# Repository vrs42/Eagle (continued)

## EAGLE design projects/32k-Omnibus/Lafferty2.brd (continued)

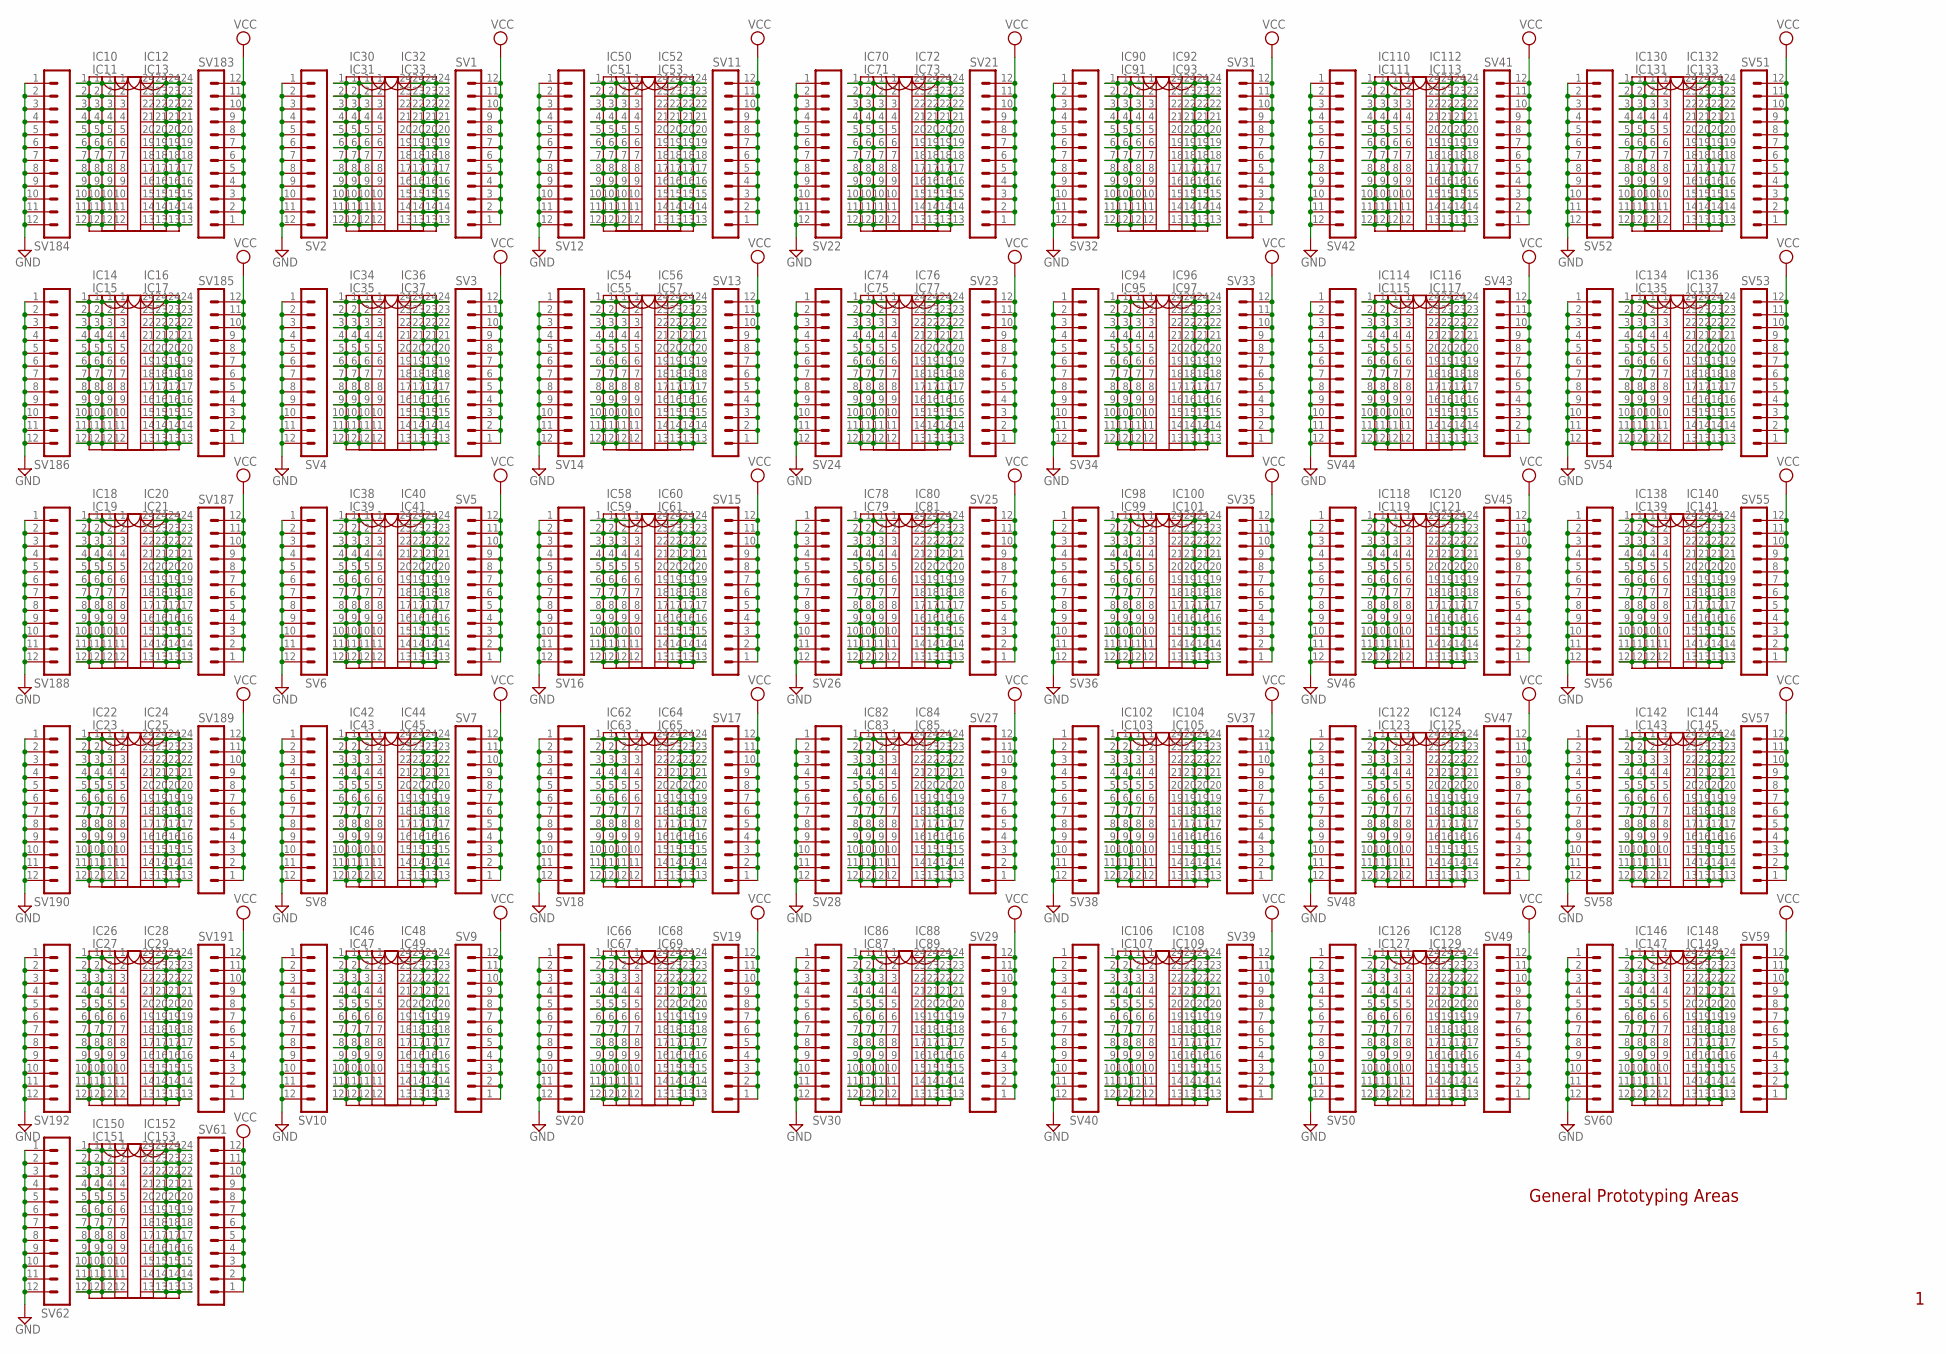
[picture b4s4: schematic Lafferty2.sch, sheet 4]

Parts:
IC10, IC14, IC18, IC22, IC26, IC30, IC34, IC38, IC42, IC46, IC50, IC54, IC58, IC62, IC66, IC70, IC74, IC78, IC82, IC86, IC90, IC94, IC98, IC102, IC106, IC110, IC114, IC118, IC122, IC126, IC130, IC134, IC138, IC142, IC146, IC150: DIL24-3
IC11, IC13, IC15, IC17, IC19, IC21, IC23, IC25, IC27, IC29, IC31, IC33, IC35, IC37, IC39, IC41, IC43, IC45, IC47, IC49, IC51, IC53, IC55, IC57, IC59, IC61, IC63, IC65, IC67, IC69, IC71, IC73, IC75, IC77, IC79, IC81, IC83, IC85, IC87, IC89, IC91, IC93, IC95, IC97, IC99, IC101, IC103, IC105, IC107, IC109, IC111, IC113, IC115, IC117, IC119, IC121, IC123, IC125, IC127, IC129, IC131, IC133, IC135, IC137, IC139, IC141, IC143, IC145, IC147, IC149, IC151, IC153: DIL24-6
IC12, IC16, IC20, IC24, IC28, IC32, IC36, IC40, IC44, IC48, IC52, IC56, IC60, IC64, IC68, IC72, IC76, IC80, IC84, IC88, IC92, IC96, IC100, IC104, IC108, IC112, IC116, IC120, IC124, IC128, IC132, IC136, IC140, IC144, IC148, IC152: DIL24-9
SV1, SV2, SV3, SV4, SV5, SV6, SV7, SV8, SV9, SV10, SV11, SV12, SV13, SV14, SV15, SV16, SV17, SV18, SV19, SV20, SV21, SV22, SV23, SV24, SV25, SV26, SV27, SV28, SV29, SV30, SV31, SV32, SV33, SV34, SV35, SV36, SV37, SV38, SV39, SV40, SV41, SV42, SV43, SV44, SV45, SV46, SV47, SV48, SV49, SV50, SV51, SV52, SV53, SV54, SV55, SV56, SV57, SV58, SV59, SV60, SV61, SV62, SV183, SV184, SV185, SV186, SV187, SV188, SV189, SV190, SV191, SV192: MA12-1

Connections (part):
GND: SV2.1, SV2.2, SV2.3, SV2.4, SV2.5, SV2.6, SV2.7, SV2.8, SV2.9, SV2.10, SV2.11, SV2.12, SV4.1, SV4.2, SV4.3, SV4.4, SV4.5, SV4.6, SV4.7, SV4.8, SV4.9, SV4.10, SV4.11, SV4.12, SV6.1, SV6.2, SV6.3, SV6.4, SV6.5, SV6.6, SV6.7, SV6.8, SV6.9, SV6.10, SV6.11, SV6.12, SV8.1, SV8.2, SV8.3, SV8.4, SV8.5, SV8.6, SV8.7, SV8.8, SV8.9, SV8.10, SV8.11, SV8.12, SV10.1, SV10.2, SV10.3, SV10.4, SV10.5, SV10.6, SV10.7, SV10.8, SV10.9, SV10.10, SV10.11, SV10.12, SV12.1, SV12.2, SV12.3, SV12.4, SV12.5, SV12.6, SV12.7, SV12.8, SV12.9, SV12.10, SV12.11, SV12.12, SV14.1, SV14.2, SV14.3, SV14.4, SV14.5, SV14.6, SV14.7, SV14.8, SV14.9, SV14.10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; also elsewhere on the board
unnamed: IC30.1, IC31.1, IC32.1, IC33.1
unnamed: IC30.2, IC31.2, IC32.2, IC33.2
unnamed: IC30.3, IC31.3, IC32.3, IC33.3
unnamed: IC30.4, IC31.4, IC32.4, IC33.4
unnamed: IC30.5, IC31.5, IC32.5, IC33.5
unnamed: IC30.6, IC31.6, IC32.6, IC33.6
unnamed: IC30.7, IC31.7, IC32.7, IC33.7
unnamed: IC10.1, IC11.1, IC12.1, IC13.1
unnamed: IC10.2, IC11.2, IC12.2, IC13.2
unnamed: IC10.3, IC11.3, IC12.3, IC13.3
unnamed: IC10.4, IC11.4, IC12.4, IC13.4
unnamed: IC10.5, IC11.5, IC12.5, IC13.5
unnamed: IC10.6, IC11.6, IC12.6, IC13.6
unnamed: IC10.7, IC11.7, IC12.7, IC13.7
unnamed: IC10.8, IC11.8, IC12.8, IC13.8
unnamed: IC10.9, IC11.9, IC12.9, IC13.9
unnamed: IC10.10, IC11.10, IC12.10, IC13.10
unnamed: IC10.11, IC11.11, IC12.11, IC13.11
unnamed: IC10.12, IC11.12, IC12.12, IC13.12
unnamed: IC10.13, IC11.13, IC12.13, IC13.13
unnamed: IC10.14, IC11.14, IC12.14, IC13.14
unnamed: IC10.15, IC11.15, IC12.15, IC13.15
unnamed: IC10.16, IC11.16, IC12.16, IC13.16
unnamed: IC10.17, IC11.17, IC12.17, IC13.17
unnamed: IC10.18, IC11.18, IC12.18, IC13.18
unnamed: IC10.19, IC11.19, IC12.19, IC13.19
unnamed: IC10.20, IC11.20, IC12.20, IC13.20
unnamed: IC10.21, IC11.21, IC12.21, IC13.21
unnamed: IC10.22, IC11.22, IC12.22, IC13.22
unnamed: IC10.23, IC11.23, IC12.23, IC13.23
unnamed: IC10.24, IC11.24, IC12.24, IC13.24
unnamed: IC14.1, IC15.1, IC16.1, IC17.1
unnamed: IC14.2, IC15.2, IC16.2, IC17.2
unnamed: IC14.3, IC15.3, IC16.3, IC17.3
unnamed: IC14.4, IC15.4, IC16.4, IC17.4
unnamed: IC14.5, IC15.5, IC16.5, IC17.5
unnamed: IC14.6, IC15.6, IC16.6, IC17.6
unnamed: IC14.7, IC15.7, IC16.7, IC17.7
unnamed: IC14.8, IC15.8, IC16.8, IC17.8
unnamed: IC14.9, IC15.9, IC16.9, IC17.9
unnamed: IC14.10, IC15.10, IC16.10, IC17.10
unnamed: IC14.11, IC15.11, IC16.11, IC17.11
unnamed: IC14.12, IC15.12, IC16.12, IC17.12
unnamed: IC14.13, IC15.13, IC16.13, IC17.13
unnamed: IC14.14, IC15.14, IC16.14, IC17.14
unnamed: IC14.15, IC15.15, IC16.15, IC17.15
unnamed: IC14.16, IC15.16, IC16.16, IC17.16
unnamed: IC14.17, IC15.17, IC16.17, IC17.17
unnamed: IC14.18, IC15.18, IC16.18, IC17.18
unnamed: IC14.19, IC15.19, IC16.19, IC17.19
unnamed: IC14.20, IC15.20, IC16.20, IC17.20
unnamed: IC14.21, IC15.21, IC16.21, IC17.21
unnamed: IC14.22, IC15.22, IC16.22, IC17.22
unnamed: IC14.23, IC15.23, IC16.23, IC17.23
unnamed: IC14.24, IC15.24, IC16.24, IC17.24
unnamed: IC18.1, IC19.1, IC20.1, IC21.1
unnamed: IC18.2, IC19.2, IC20.2, IC21.2
unnamed: IC18.3, IC19.3, IC20.3, IC21.3
unnamed: IC18.4, IC19.4, IC20.4, IC21.4
unnamed: IC18.5, IC19.5, IC20.5, IC21.5
unnamed: IC18.6, IC19.6, IC20.6, IC21.6
unnamed: IC18.7, IC19.7, IC20.7, IC21.7
unnamed: IC18.8, IC19.8, IC20.8, IC21.8
unnamed: IC18.9, IC19.9, IC20.9, IC21.9
unnamed: IC18.10, IC19.10, IC20.10, IC21.10
unnamed: IC18.11, IC19.11, IC20.11, IC21.11
unnamed: IC18.12, IC19.12, IC20.12, IC21.12
unnamed: IC18.13, IC19.13, IC20.13, IC21.13
unnamed: IC18.14, IC19.14, IC20.14, IC21.14
unnamed: IC18.15, IC19.15, IC20.15, IC21.15
unnamed: IC18.16, IC19.16, IC20.16, IC21.16
unnamed: IC18.17, IC19.17, IC20.17, IC21.17
unnamed: IC18.18, IC19.18, IC20.18, IC21.18
unnamed: IC18.19, IC19.19, IC20.19, IC21.19
unnamed: IC18.20, IC19.20, IC20.20, IC21.20
unnamed: IC18.21, IC19.21, IC20.21, IC21.21
unnamed: IC18.22, IC19.22, IC20.22, IC21.22
unnamed: IC18.23, IC19.23, IC20.23, IC21.23
unnamed: IC18.24, IC19.24, IC20.24, IC21.24
unnamed: IC22.1, IC23.1, IC24.1, IC25.1
unnamed: IC22.2, IC23.2, IC24.2, IC25.2
unnamed: IC22.3, IC23.3, IC24.3, IC25.3
unnamed: IC22.4, IC23.4, IC24.4, IC25.4
unnamed: IC22.5, IC23.5, IC24.5, IC25.5
unnamed: IC22.6, IC23.6, IC24.6, IC25.6
unnamed: IC22.7, IC23.7, IC24.7, IC25.7
unnamed: IC22.8, IC23.8, IC24.8, IC25.8
unnamed: IC22.9, IC23.9, IC24.9, IC25.9
unnamed: IC22.10, IC23.10, IC24.10, IC25.10
unnamed: IC22.11, IC23.11, IC24.11, IC25.11
unnamed: IC22.12, IC23.12, IC24.12, IC25.12
unnamed: IC22.13, IC23.13, IC24.13, IC25.13
unnamed: IC22.14, IC23.14, IC24.14, IC25.14
unnamed: IC22.15, IC23.15, IC24.15, IC25.15
unnamed: IC22.16, IC23.16, IC24.16, IC25.16
unnamed: IC22.17, IC23.17, IC24.17, IC25.17
unnamed: IC22.18, IC23.18, IC24.18, IC25.18
unnamed: IC22.19, IC23.19, IC24.19, IC25.19
unnamed: IC22.20, IC23.20, IC24.20, IC25.20
unnamed: IC22.21, IC23.21, IC24.21, IC25.21
unnamed: IC22.22, IC23.22, IC24.22, IC25.22
unnamed: IC22.23, IC23.23, IC24.23, IC25.23
unnamed: IC22.24, IC23.24, IC24.24, IC25.24
unnamed: IC26.1, IC27.1, IC28.1, IC29.1
unnamed: IC26.2, IC27.2, IC28.2, IC29.2
unnamed: IC26.3, IC27.3, IC28.3, IC29.3
unnamed: IC26.4, IC27.4, IC28.4, IC29.4
unnamed: IC26.5, IC27.5, IC28.5, IC29.5
unnamed: IC26.6, IC27.6, IC28.6, IC29.6
unnamed: IC26.7, IC27.7, IC28.7, IC29.7
unnamed: IC26.8, IC27.8, IC28.8, IC29.8
unnamed: IC26.9, IC27.9, IC28.9, IC29.9
unnamed: IC26.10, IC27.10, IC28.10, IC29.10
unnamed: IC26.11, IC27.11, IC28.11, IC29.11
unnamed: IC26.12, IC27.12, IC28.12, IC29.12
unnamed: IC26.13, IC27.13, IC28.13, IC29.13
unnamed: IC26.14, IC27.14, IC28.14, IC29.14
unnamed: IC26.15, IC27.15, IC28.15, IC29.15
unnamed: IC26.16, IC27.16, IC28.16, IC29.16
unnamed: IC26.17, IC27.17, IC28.17, IC29.17
unnamed: IC26.18, IC27.18, IC28.18, IC29.18
unnamed: IC26.19, IC27.19, IC28.19, IC29.19
unnamed: IC26.20, IC27.20, IC28.20, IC29.20
unnamed: IC26.21, IC27.21, IC28.21, IC29.21
unnamed: IC26.22, IC27.22, IC28.22, IC29.22
unnamed: IC26.23, IC27.23, IC28.23, IC29.23
unnamed: IC26.24, IC27.24, IC28.24, IC29.24
unnamed: IC30.8, IC31.8, IC32.8, IC33.8
unnamed: IC30.9, IC31.9, IC32.9, IC33.9
unnamed: IC30.10, IC31.10, IC32.10, IC33.10
unnamed: IC30.11, IC31.11, IC32.11, IC33.11
unnamed: IC30.12, IC31.12, IC32.12, IC33.12
unnamed: IC30.13, IC31.13, IC32.13, IC33.13
unnamed: IC30.14, IC31.14, IC32.14, IC33.14
unnamed: IC30.15, IC31.15, IC32.15, IC33.15
unnamed: IC30.16, IC31.16, IC32.16, IC33.16
unnamed: IC30.17, IC31.17, IC32.17, IC33.17
unnamed: IC30.18, IC31.18, IC32.18, IC33.18
unnamed: IC30.19, IC31.19, IC32.19, IC33.19
unnamed: IC30.20, IC31.20, IC32.20, IC33.20
unnamed: IC30.21, IC31.21, IC32.21, IC33.21
unnamed: IC30.22, IC31.22, IC32.22, IC33.22
unnamed: IC30.23, IC31.23, IC32.23, IC33.23
unnamed: IC30.24, IC31.24, IC32.24, IC33.24
unnamed: IC34.1, IC35.1, IC36.1, IC37.1
unnamed: IC34.2, IC35.2, IC36.2, IC37.2
unnamed: IC34.3, IC35.3, IC36.3, IC37.3
unnamed: IC34.4, IC35.4, IC36.4, IC37.4
unnamed: IC34.5, IC35.5, IC36.5, IC37.5
unnamed: IC34.6, IC35.6, IC36.6, IC37.6
unnamed: IC34.7, IC35.7, IC36.7, IC37.7
unnamed: IC34.8, IC35.8, IC36.8, IC37.8
unnamed: IC34.9, IC35.9, IC36.9, IC37.9
unnamed: IC34.10, IC35.10, IC36.10, IC37.10
unnamed: IC34.11, IC35.11, IC36.11, IC37.11
unnamed: IC34.12, IC35.12, IC36.12, IC37.12
unnamed: IC34.13, IC35.13, IC36.13, IC37.13
unnamed: IC34.14, IC35.14, IC36.14, IC37.14
unnamed: IC34.15, IC35.15, IC36.15, IC37.15
unnamed: IC34.16, IC35.16, IC36.16, IC37.16
unnamed: IC34.17, IC35.17, IC36.17, IC37.17
unnamed: IC34.18, IC35.18, IC36.18, IC37.18
unnamed: IC34.19, IC35.19, IC36.19, IC37.19
unnamed: IC34.20, IC35.20, IC36.20, IC37.20
unnamed: IC34.21, IC35.21, IC36.21, IC37.21
unnamed: IC34.22, IC35.22, IC36.22, IC37.22
unnamed: IC34.23, IC35.23, IC36.23, IC37.23
unnamed: IC34.24, IC35.24, IC36.24, IC37.24
unnamed: IC38.1, IC39.1, IC40.1, IC41.1
unnamed: IC38.2, IC39.2, IC40.2, IC41.2
unnamed: IC38.3, IC39.3, IC40.3, IC41.3
unnamed: IC38.4, IC39.4, IC40.4, IC41.4
unnamed: IC38.5, IC39.5, IC40.5, IC41.5
unnamed: IC38.6, IC39.6, IC40.6, IC41.6
unnamed: IC38.7, IC39.7, IC40.7, IC41.7
unnamed: IC38.8, IC39.8, IC40.8, IC41.8
unnamed: IC38.9, IC39.9, IC40.9, IC41.9
unnamed: IC38.10, IC39.10, IC40.10, IC41.10
unnamed: IC38.11, IC39.11, IC40.11, IC41.11
unnamed: IC38.12, IC39.12, IC40.12, IC41.12
unnamed: IC38.13, IC39.13, IC40.13, IC41.13
unnamed: IC38.14, IC39.14, IC40.14, IC41.14
unnamed: IC38.15, IC39.15, IC40.15, IC41.15
unnamed: IC38.16, IC39.16, IC40.16, IC41.16
unnamed: IC38.17, IC39.17, IC40.17, IC41.17
unnamed: IC38.18, IC39.18, IC40.18, IC41.18
unnamed: IC38.19, IC39.19, IC40.19, IC41.19
unnamed: IC38.20, IC39.20, IC40.20, IC41.20
unnamed: IC38.21, IC39.21, IC40.21, IC41.21
unnamed: IC38.22, IC39.22, IC40.22, IC41.22
unnamed: IC38.23, IC39.23, IC40.23, IC41.23
unnamed: IC38.24, IC39.24, IC40.24, IC41.24
unnamed: IC42.1, IC43.1, IC44.1, IC45.1
unnamed: IC42.2, IC43.2, IC44.2, IC45.2
unnamed: IC42.3, IC43.3, IC44.3, IC45.3
unnamed: IC42.4, IC43.4, IC44.4, IC45.4
unnamed: IC42.5, IC43.5, IC44.5, IC45.5
unnamed: IC42.6, IC43.6, IC44.6, IC45.6
unnamed: IC42.7, IC43.7, IC44.7, IC45.7
unnamed: IC42.8, IC43.8, IC44.8, IC45.8
unnamed: IC42.9, IC43.9, IC44.9, IC45.9
unnamed: IC42.10, IC43.10, IC44.10, IC45.10
unnamed: IC42.11, IC43.11, IC44.11, IC45.11
unnamed: IC42.12, IC43.12, IC44.12, IC45.12
unnamed: IC42.13, IC43.13, IC44.13, IC45.13
unnamed: IC42.14, IC43.14, IC44.14, IC45.14
unnamed: IC42.15, IC43.15, IC44.15, IC45.15
unnamed: IC42.16, IC43.16, IC44.16, IC45.16
unnamed: IC42.17, IC43.17, IC44.17, IC45.17
unnamed: IC42.18, IC43.18, IC44.18, IC45.18
unnamed: IC42.19, IC43.19, IC44.19, IC45.19
unnamed: IC42.20, IC43.20, IC44.20, IC45.20
unnamed: IC42.21, IC43.21, IC44.21, IC45.21
unnamed: IC42.22, IC43.22, IC44.22, IC45.22
unnamed: IC42.23, IC43.23, IC44.23, IC45.23
unnamed: IC42.24, IC43.24, IC44.24, IC45.24
unnamed: IC46.1, IC47.1, IC48.1, IC49.1
unnamed: IC46.2, IC47.2, IC48.2, IC49.2
unnamed: IC46.3, IC47.3, IC48.3, IC49.3
unnamed: IC46.4, IC47.4, IC48.4, IC49.4
unnamed: IC46.5, IC47.5, IC48.5, IC49.5
unnamed: IC46.6, IC47.6, IC48.6, IC49.6
unnamed: IC46.7, IC47.7, IC48.7, IC49.7
unnamed: IC46.8, IC47.8, IC48.8, IC49.8
unnamed: IC46.9, IC47.9, IC48.9, IC49.9
unnamed: IC46.10, IC47.10, IC48.10, IC49.10
unnamed: IC46.11, IC47.11, IC48.11, IC49.11
unnamed: IC46.12, IC47.12, IC48.12, IC49.12
unnamed: IC46.13, IC47.13, IC48.13, IC49.13
unnamed: IC46.14, IC47.14, IC48.14, IC49.14
unnamed: IC46.15, IC47.15, IC48.15, IC49.15
unnamed: IC46.16, IC47.16, IC48.16, IC49.16
unnamed: IC46.17, IC47.17, IC48.17, IC49.17
unnamed: IC46.18, IC47.18, IC48.18, IC49.18
unnamed: IC46.19, IC47.19, IC48.19, IC49.19
unnamed: IC46.20, IC47.20, IC48.20, IC49.20
unnamed: IC46.21, IC47.21, IC48.21, IC49.21
unnamed: IC46.22, IC47.22, IC48.22, IC49.22
unnamed: IC46.23, IC47.23, IC48.23, IC49.23
unnamed: IC46.24, IC47.24, IC48.24, IC49.24
unnamed: IC50.1, IC51.1, IC52.1, IC53.1
unnamed: IC50.2, IC51.2, IC52.2, IC53.2
unnamed: IC50.3, IC51.3, IC52.3, IC53.3
unnamed: IC50.4, IC51.4, IC52.4, IC53.4
unnamed: IC50.5, IC51.5, IC52.5, IC53.5
unnamed: IC50.6, IC51.6, IC52.6, IC53.6
unnamed: IC50.7, IC51.7, IC52.7, IC53.7
unnamed: IC50.8, IC51.8, IC52.8, IC53.8
unnamed: IC50.9, IC51.9, IC52.9, IC53.9
unnamed: IC50.10, IC51.10, IC52.10, IC53.10
unnamed: IC50.11, IC51.11, IC52.11, IC53.11
unnamed: IC50.12, IC51.12, IC52.12, IC53.12
unnamed: IC50.13, IC51.13, IC52.13, IC53.13
unnamed: IC50.14, IC51.14, IC52.14, IC53.14
unnamed: IC50.15, IC51.15, IC52.15, IC53.15
unnamed: IC50.16, IC51.16, IC52.16, IC53.16
unnamed: IC50.17, IC51.17, IC52.17, IC53.17
unnamed: IC50.18, IC51.18, IC52.18, IC53.18
unnamed: IC50.19, IC51.19, IC52.19, IC53.19
unnamed: IC50.20, IC51.20, IC52.20, IC53.20
unnamed: IC50.21, IC51.21, IC52.21, IC53.21
unnamed: IC50.22, IC51.22, IC52.22, IC53.22
unnamed: IC50.23, IC51.23, IC52.23, IC53.23
unnamed: IC50.24, IC51.24, IC52.24, IC53.24
unnamed: IC54.1, IC55.1, IC56.1, IC57.1
unnamed: IC54.2, IC55.2, IC56.2, IC57.2
unnamed: IC54.3, IC55.3, IC56.3, IC57.3
unnamed: IC54.4, IC55.4, IC56.4, IC57.4
unnamed: IC54.5, IC55.5, IC56.5, IC57.5
unnamed: IC54.6, IC55.6, IC56.6, IC57.6
unnamed: IC54.7, IC55.7, IC56.7, IC57.7
unnamed: IC54.8, IC55.8, IC56.8, IC57.8
unnamed: IC54.9, IC55.9, IC56.9, IC57.9
unnamed: IC54.10, IC55.10, IC56.10, IC57.10
unnamed: IC54.11, IC55.11, IC56.11, IC57.11
unnamed: IC54.12, IC55.12, IC56.12, IC57.12
unnamed: IC54.13, IC55.13, IC56.13, IC57.13
unnamed: IC54.14, IC55.14, IC56.14, IC57.14
unnamed: IC54.15, IC55.15, IC56.15, IC57.15
unnamed: IC54.16, IC55.16, IC56.16, IC57.16
unnamed: IC54.17, IC55.17, IC56.17, IC57.17
unnamed: IC54.18, IC55.18, IC56.18, IC57.18
unnamed: IC54.19, IC55.19, IC56.19, IC57.19
unnamed: IC54.20, IC55.20, IC56.20, IC57.20
unnamed: IC54.21, IC55.21, IC56.21, IC57.21
unnamed: IC54.22, IC55.22, IC56.22, IC57.22
unnamed: IC54.23, IC55.23, IC56.23, IC57.23
unnamed: IC54.24, IC55.24, IC56.24, IC57.24
unnamed: IC58.1, IC59.1, IC60.1, IC61.1
unnamed: IC58.2, IC59.2, IC60.2, IC61.2
unnamed: IC58.3, IC59.3, IC60.3, IC61.3
unnamed: IC58.4, IC59.4, IC60.4, IC61.4
unnamed: IC58.5, IC59.5, IC60.5, IC61.5
unnamed: IC58.6, IC59.6, IC60.6, IC61.6
unnamed: IC58.7, IC59.7, IC60.7, IC61.7
unnamed: IC58.8, IC59.8, IC60.8, IC61.8
unnamed: IC58.9, IC59.9, IC60.9, IC61.9
unnamed: IC58.10, IC59.10, IC60.10, IC61.10
unnamed: IC58.11, IC59.11, IC60.11, IC61.11
unnamed: IC58.12, IC59.12, IC60.12, IC61.12
unnamed: IC58.13, IC59.13, IC60.13, IC61.13
unnamed: IC58.14, IC59.14, IC60.14, IC61.14
unnamed: IC58.15, IC59.15, IC60.15, IC61.15
unnamed: IC58.16, IC59.16, IC60.16, IC61.16
unnamed: IC58.17, IC59.17, IC60.17, IC61.17
unnamed: IC58.18, IC59.18, IC60.18, IC61.18
unnamed: IC58.19, IC59.19, IC60.19, IC61.19
unnamed: IC58.20, IC59.20, IC60.20, IC61.20
unnamed: IC58.21, IC59.21, IC60.21, IC61.21
unnamed: IC58.22, IC59.22, IC60.22, IC61.22
unnamed: IC58.23, IC59.23, IC60.23, IC61.23
unnamed: IC58.24, IC59.24, IC60.24, IC61.24
unnamed: IC62.1, IC63.1, IC64.1, IC65.1
unnamed: IC62.2, IC63.2, IC64.2, IC65.2
unnamed: IC62.3, IC63.3, IC64.3, IC65.3
unnamed: IC62.4, IC63.4, IC64.4, IC65.4
unnamed: IC62.5, IC63.5, IC64.5, IC65.5
unnamed: IC62.6, IC63.6, IC64.6, IC65.6
unnamed: IC62.7, IC63.7, IC64.7, IC65.7
unnamed: IC62.8, IC63.8, IC64.8, IC65.8
unnamed: IC62.9, IC63.9, IC64.9, IC65.9
unnamed: IC62.10, IC63.10, IC64.10, IC65.10
unnamed: IC62.11, IC63.11, IC64.11, IC65.11
unnamed: IC62.12, IC63.12, IC64.12, IC65.12
unnamed: IC62.13, IC63.13, IC64.13, IC65.13
unnamed: IC62.14, IC63.14, IC64.14, IC65.14
unnamed: IC62.15, IC63.15, IC64.15, IC65.15
unnamed: IC62.16, IC63.16, IC64.16, IC65.16
unnamed: IC62.17, IC63.17, IC64.17, IC65.17
unnamed: IC62.18, IC63.18, IC64.18, IC65.18
unnamed: IC62.19, IC63.19, IC64.19, IC65.19
unnamed: IC62.20, IC63.20, IC64.20, IC65.20
unnamed: IC62.21, IC63.21, IC64.21, IC65.21
unnamed: IC62.22, IC63.22, IC64.22, IC65.22
unnamed: IC62.23, IC63.23, IC64.23, IC65.23
unnamed: IC62.24, IC63.24, IC64.24, IC65.24
unnamed: IC66.1, IC67.1, IC68.1, IC69.1
unnamed: IC66.2, IC67.2, IC68.2, IC69.2
unnamed: IC66.3, IC67.3, IC68.3, IC69.3
unnamed: IC66.4, IC67.4, IC68.4, IC69.4
unnamed: IC66.5, IC67.5, IC68.5, IC69.5
unnamed: IC66.6, IC67.6, IC68.6, IC69.6
unnamed: IC66.7, IC67.7, IC68.7, IC69.7
unnamed: IC66.8, IC67.8, IC68.8, IC69.8
unnamed: IC66.9, IC67.9, IC68.9, IC69.9
unnamed: IC66.10, IC67.10, IC68.10, IC69.10
unnamed: IC66.11, IC67.11, IC68.11, IC69.11
unnamed: IC66.12, IC67.12, IC68.12, IC69.12
unnamed: IC66.13, IC67.13, IC68.13, IC69.13
unnamed: IC66.14, IC67.14, IC68.14, IC69.14
unnamed: IC66.15, IC67.15, IC68.15, IC69.15
unnamed: IC66.16, IC67.16, IC68.16, IC69.16
unnamed: IC66.17, IC67.17, IC68.17, IC69.17
unnamed: IC66.18, IC67.18, IC68.18, IC69.18
unnamed: IC66.19, IC67.19, IC68.19, IC69.19
unnamed: IC66.20, IC67.20, IC68.20, IC69.20
unnamed: IC66.21, IC67.21, IC68.21, IC69.21
unnamed: IC66.22, IC67.22, IC68.22, IC69.22
unnamed: IC66.23, IC67.23, IC68.23, IC69.23
unnamed: IC66.24, IC67.24, IC68.24, IC69.24
unnamed: IC70.1, IC71.1, IC72.1, IC73.1
unnamed: IC70.2, IC71.2, IC72.2, IC73.2
unnamed: IC70.3, IC71.3, IC72.3, IC73.3
unnamed: IC70.4, IC71.4, IC72.4, IC73.4
unnamed: IC70.5, IC71.5, IC72.5, IC73.5
unnamed: IC70.6, IC71.6, IC72.6, IC73.6
unnamed: IC70.7, IC71.7, IC72.7, IC73.7
unnamed: IC70.8, IC71.8, IC72.8, IC73.8
unnamed: IC70.9, IC71.9, IC72.9, IC73.9
unnamed: IC70.10, IC71.10, IC72.10, IC73.10
unnamed: IC70.11, IC71.11, IC72.11, IC73.11
unnamed: IC70.12, IC71.12, IC72.12, IC73.12
unnamed: IC70.13, IC71.13, IC72.13, IC73.13
unnamed: IC70.14, IC71.14, IC72.14, IC73.14
unnamed: IC70.15, IC71.15, IC72.15, IC73.15
unnamed: IC70.16, IC71.16, IC72.16, IC73.16
unnamed: IC70.17, IC71.17, IC72.17, IC73.17
unnamed: IC70.18, IC71.18, IC72.18, IC73.18
unnamed: IC70.19, IC71.19, IC72.19, IC73.19
unnamed: IC70.20, IC71.20, IC72.20, IC73.20
unnamed: IC70.21, IC71.21, IC72.21, IC73.21
unnamed: IC70.22, IC71.22, IC72.22, IC73.22
unnamed: IC70.23, IC71.23, IC72.23, IC73.23
unnamed: IC70.24, IC71.24, IC72.24, IC73.24
unnamed: IC74.1, IC75.1, IC76.1, IC77.1
unnamed: IC74.2, IC75.2, IC76.2, IC77.2
unnamed: IC74.3, IC75.3, IC76.3, IC77.3
unnamed: IC74.4, IC75.4, IC76.4, IC77.4
unnamed: IC74.5, IC75.5, IC76.5, IC77.5
unnamed: IC74.6, IC75.6, IC76.6, IC77.6
unnamed: IC74.7, IC75.7, IC76.7, IC77.7
unnamed: IC74.8, IC75.8, IC76.8, IC77.8
unnamed: IC74.9, IC75.9, IC76.9, IC77.9
unnamed: IC74.10, IC75.10, IC76.10, IC77.10
unnamed: IC74.11, IC75.11, IC76.11, IC77.11
unnamed: IC74.12, IC75.12, IC76.12, IC77.12
unnamed: IC74.13, IC75.13, IC76.13, IC77.13
unnamed: IC74.14, IC75.14, IC76.14, IC77.14
unnamed: IC74.15, IC75.15, IC76.15, IC77.15
unnamed: IC74.16, IC75.16, IC76.16, IC77.16
unnamed: IC74.17, IC75.17, IC76.17, IC77.17
unnamed: IC74.18, IC75.18, IC76.18, IC77.18
unnamed: IC74.19, IC75.19, IC76.19, IC77.19
unnamed: IC74.20, IC75.20, IC76.20, IC77.20
unnamed: IC74.21, IC75.21, IC76.21, IC77.21
unnamed: IC74.22, IC75.22, IC76.22, IC77.22
unnamed: IC74.23, IC75.23, IC76.23, IC77.23
unnamed: IC74.24, IC75.24, IC76.24, IC77.24
unnamed: IC78.1, IC79.1, IC80.1, IC81.1
unnamed: IC78.2, IC79.2, IC80.2, IC81.2
unnamed: IC78.3, IC79.3, IC80.3, IC81.3
unnamed: IC78.4, IC79.4, IC80.4, IC81.4
unnamed: IC78.5, IC79.5, IC80.5, IC81.5
unnamed: IC78.6, IC79.6, IC80.6, IC81.6
unnamed: IC78.7, IC79.7, IC80.7, IC81.7
unnamed: IC78.8, IC79.8, IC80.8, IC81.8
unnamed: IC78.9, IC79.9, IC80.9, IC81.9
unnamed: IC78.10, IC79.10, IC80.10, IC81.10
unnamed: IC78.11, IC79.11, IC80.11, IC81.11
unnamed: IC78.12, IC79.12, IC80.12, IC81.12
unnamed: IC78.13, IC79.13, IC80.13, IC81.13
unnamed: IC78.14, IC79.14, IC80.14, IC81.14
unnamed: IC78.15, IC79.15, IC80.15, IC81.15
unnamed: IC78.16, IC79.16, IC80.16, IC81.16
unnamed: IC78.17, IC79.17, IC80.17, IC81.17
unnamed: IC78.18, IC79.18, IC80.18, IC81.18
unnamed: IC78.19, IC79.19, IC80.19, IC81.19
unnamed: IC78.20, IC79.20, IC80.20, IC81.20
unnamed: IC78.21, IC79.21, IC80.21, IC81.21
unnamed: IC78.22, IC79.22, IC80.22, IC81.22
unnamed: IC78.23, IC79.23, IC80.23, IC81.23
unnamed: IC78.24, IC79.24, IC80.24, IC81.24
unnamed: IC82.1, IC83.1, IC84.1, IC85.1
unnamed: IC82.2, IC83.2, IC84.2, IC85.2
unnamed: IC82.3, IC83.3, IC84.3, IC85.3
unnamed: IC82.4, IC83.4, IC84.4, IC85.4
unnamed: IC82.5, IC83.5, IC84.5, IC85.5
unnamed: IC82.6, IC83.6, IC84.6, IC85.6
unnamed: IC82.7, IC83.7, IC84.7, IC85.7
unnamed: IC82.8, IC83.8, IC84.8, IC85.8
unnamed: IC82.9, IC83.9, IC84.9, IC85.9
unnamed: IC82.10, IC83.10, IC84.10, IC85.10
unnamed: IC82.11, IC83.11, IC84.11, IC85.11
unnamed: IC82.12, IC83.12, IC84.12, IC85.12
unnamed: IC82.13, IC83.13, IC84.13, IC85.13
unnamed: IC82.14, IC83.14, IC84.14, IC85.14
unnamed: IC82.15, IC83.15, IC84.15, IC85.15
unnamed: IC82.16, IC83.16, IC84.16, IC85.16
unnamed: IC82.17, IC83.17, IC84.17, IC85.17
unnamed: IC82.18, IC83.18, IC84.18, IC85.18
unnamed: IC82.19, IC83.19, IC84.19, IC85.19
unnamed: IC82.20, IC83.20, IC84.20, IC85.20
unnamed: IC82.21, IC83.21, IC84.21, IC85.21
unnamed: IC82.22, IC83.22, IC84.22, IC85.22
unnamed: IC82.23, IC83.23, IC84.23, IC85.23
unnamed: IC82.24, IC83.24, IC84.24, IC85.24
unnamed: IC86.1, IC87.1, IC88.1, IC89.1
unnamed: IC86.2, IC87.2, IC88.2, IC89.2
unnamed: IC86.3, IC87.3, IC88.3, IC89.3
unnamed: IC86.4, IC87.4, IC88.4, IC89.4
unnamed: IC86.5, IC87.5, IC88.5, IC89.5
unnamed: IC86.6, IC87.6, IC88.6, IC89.6
unnamed: IC86.7, IC87.7, IC88.7, IC89.7
unnamed: IC86.8, IC87.8, IC88.8, IC89.8
unnamed: IC86.9, IC87.9, IC88.9, IC89.9
unnamed: IC86.10, IC87.10, IC88.10, IC89.10
unnamed: IC86.11, IC87.11, IC88.11, IC89.11
unnamed: IC86.12, IC87.12, IC88.12, IC89.12
unnamed: IC86.13, IC87.13, IC88.13, IC89.13
unnamed: IC86.14, IC87.14, IC88.14, IC89.14
unnamed: IC86.15, IC87.15, IC88.15, IC89.15
unnamed: IC86.16, IC87.16, IC88.16, IC89.16
unnamed: IC86.17, IC87.17, IC88.17, IC89.17
unnamed: IC86.18, IC87.18, IC88.18, IC89.18
unnamed: IC86.19, IC87.19, IC88.19, IC89.19
unnamed: IC86.20, IC87.20, IC88.20, IC89.20
unnamed: IC86.21, IC87.21, IC88.21, IC89.21
unnamed: IC86.22, IC87.22, IC88.22, IC89.22
unnamed: IC86.23, IC87.23, IC88.23, IC89.23
unnamed: IC86.24, IC87.24, IC88.24, IC89.24
unnamed: IC90.1, IC91.1, IC92.1, IC93.1
unnamed: IC90.2, IC91.2, IC92.2, IC93.2
unnamed: IC90.3, IC91.3, IC92.3, IC93.3
unnamed: IC90.4, IC91.4, IC92.4, IC93.4
unnamed: IC90.5, IC91.5, IC92.5, IC93.5
unnamed: IC90.6, IC91.6, IC92.6, IC93.6
unnamed: IC90.7, IC91.7, IC92.7, IC93.7
unnamed: IC90.8, IC91.8, IC92.8, IC93.8
unnamed: IC90.9, IC91.9, IC92.9, IC93.9
unnamed: IC90.10, IC91.10, IC92.10, IC93.10
unnamed: IC90.11, IC91.11, IC92.11, IC93.11
unnamed: IC90.12, IC91.12, IC92.12, IC93.12
unnamed: IC90.13, IC91.13, IC92.13, IC93.13
unnamed: IC90.14, IC91.14, IC92.14, IC93.14
unnamed: IC90.15, IC91.15, IC92.15, IC93.15
unnamed: IC90.16, IC91.16, IC92.16, IC93.16
unnamed: IC90.17, IC91.17, IC92.17, IC93.17
unnamed: IC90.18, IC91.18, IC92.18, IC93.18
unnamed: IC90.19, IC91.19, IC92.19, IC93.19
unnamed: IC90.20, IC91.20, IC92.20, IC93.20
unnamed: IC90.21, IC91.21, IC92.21, IC93.21
unnamed: IC90.22, IC91.22, IC92.22, IC93.22
unnamed: IC90.23, IC91.23, IC92.23, IC93.23
unnamed: IC90.24, IC91.24, IC92.24, IC93.24
unnamed: IC94.1, IC95.1, IC96.1, IC97.1
unnamed: IC94.2, IC95.2, IC96.2, IC97.2
unnamed: IC94.3, IC95.3, IC96.3, IC97.3
unnamed: IC94.4, IC95.4, IC96.4, IC97.4
unnamed: IC94.5, IC95.5, IC96.5, IC97.5
unnamed: IC94.6, IC95.6, IC96.6, IC97.6
unnamed: IC94.7, IC95.7, IC96.7, IC97.7
unnamed: IC94.8, IC95.8, IC96.8, IC97.8
unnamed: IC94.9, IC95.9, IC96.9, IC97.9
unnamed: IC94.10, IC95.10, IC96.10, IC97.10
unnamed: IC94.11, IC95.11, IC96.11, IC97.11
unnamed: IC94.12, IC95.12, IC96.12, IC97.12
unnamed: IC94.13, IC95.13, IC96.13, IC97.13
unnamed: IC94.14, IC95.14, IC96.14, IC97.14
unnamed: IC94.15, IC95.15, IC96.15, IC97.15
unnamed: IC94.16, IC95.16, IC96.16, IC97.16
unnamed: IC94.17, IC95.17, IC96.17, IC97.17
unnamed: IC94.18, IC95.18, IC96.18, IC97.18
unnamed: IC94.19, IC95.19, IC96.19, IC97.19
unnamed: IC94.20, IC95.20, IC96.20, IC97.20
unnamed: IC94.21, IC95.21, IC96.21, IC97.21
unnamed: IC94.22, IC95.22, IC96.22, IC97.22
unnamed: IC94.23, IC95.23, IC96.23, IC97.23
unnamed: IC94.24, IC95.24, IC96.24, IC97.24
unnamed: IC98.1, IC99.1, IC100.1, IC101.1
unnamed: IC98.2, IC99.2, IC100.2, IC101.2
unnamed: IC98.3, IC99.3, IC100.3, IC101.3
unnamed: IC98.4, IC99.4, IC100.4, IC101.4
unnamed: IC98.5, IC99.5, IC100.5, IC101.5
unnamed: IC98.6, IC99.6, IC100.6, IC101.6
unnamed: IC98.7, IC99.7, IC100.7, IC101.7
unnamed: IC98.8, IC99.8, IC100.8, IC101.8
unnamed: IC98.9, IC99.9, IC100.9, IC101.9
unnamed: IC98.10, IC99.10, IC100.10, IC101.10
unnamed: IC98.11, IC99.11, IC100.11, IC101.11
unnamed: IC98.12, IC99.12, IC100.12, IC101.12
unnamed: IC98.13, IC99.13, IC100.13, IC101.13
unnamed: IC98.14, IC99.14, IC100.14, IC101.14
unnamed: IC98.15, IC99.15, IC100.15, IC101.15
unnamed: IC98.16, IC99.16, IC100.16, IC101.16
unnamed: IC98.17, IC99.17, IC100.17, IC101.17
unnamed: IC98.18, IC99.18, IC100.18, IC101.18
unnamed: IC98.19, IC99.19, IC100.19, IC101.19
unnamed: IC98.20, IC99.20, IC100.20, IC101.20
unnamed: IC98.21, IC99.21, IC100.21, IC101.21
unnamed: IC98.22, IC99.22, IC100.22, IC101.22
unnamed: IC98.23, IC99.23, IC100.23, IC101.23
unnamed: IC98.24, IC99.24, IC100.24, IC101.24
unnamed: IC102.1, IC103.1, IC104.1, IC105.1
unnamed: IC102.2, IC103.2, IC104.2, IC105.2
unnamed: IC102.3, IC103.3, IC104.3, IC105.3
unnamed: IC102.4, IC103.4, IC104.4, IC105.4
unnamed: IC102.5, IC103.5, IC104.5, IC105.5
unnamed: IC102.6, IC103.6, IC104.6, IC105.6
unnamed: IC102.7, IC103.7, IC104.7, IC105.7
unnamed: IC102.8, IC103.8, IC104.8, IC105.8
unnamed: IC102.9, IC103.9, IC104.9, IC105.9
unnamed: IC102.10, IC103.10, IC104.10, IC105.10
unnamed: IC102.11, IC103.11, IC104.11, IC105.11
unnamed: IC102.12, IC103.12, IC104.12, IC105.12
unnamed: IC102.13, IC103.13, IC104.13, IC105.13
unnamed: IC102.14, IC103.14, IC104.14, IC105.14
unnamed: IC102.15, IC103.15, IC104.15, IC105.15
unnamed: IC102.16, IC103.16, IC104.16, IC105.16
unnamed: IC102.17, IC103.17, IC104.17, IC105.17
unnamed: IC102.18, IC103.18, IC104.18, IC105.18
unnamed: IC102.19, IC103.19, IC104.19, IC105.19
unnamed: IC102.20, IC103.20, IC104.20, IC105.20
unnamed: IC102.21, IC103.21, IC104.21, IC105.21
unnamed: IC102.22, IC103.22, IC104.22, IC105.22
unnamed: IC102.23, IC103.23, IC104.23, IC105.23
unnamed: IC102.24, IC103.24, IC104.24, IC105.24
unnamed: IC106.1, IC107.1, IC108.1, IC109.1
unnamed: IC106.2, IC107.2, IC108.2, IC109.2
unnamed: IC106.3, IC107.3, IC108.3, IC109.3
unnamed: IC106.4, IC107.4, IC108.4, IC109.4
unnamed: IC106.5, IC107.5, IC108.5, IC109.5
unnamed: IC106.6, IC107.6, IC108.6, IC109.6
unnamed: IC106.7, IC107.7, IC108.7, IC109.7
unnamed: IC106.8, IC107.8, IC108.8, IC109.8
unnamed: IC106.9, IC107.9, IC108.9, IC109.9
unnamed: IC106.10, IC107.10, IC108.10, IC109.10
unnamed: IC106.11, IC107.11, IC108.11, IC109.11
unnamed: IC106.12, IC107.12, IC108.12, IC109.12
unnamed: IC106.13, IC107.13, IC108.13, IC109.13
unnamed: IC106.14, IC107.14, IC108.14, IC109.14
unnamed: IC106.15, IC107.15, IC108.15, IC109.15
unnamed: IC106.16, IC107.16, IC108.16, IC109.16
unnamed: IC106.17, IC107.17, IC108.17, IC109.17
unnamed: IC106.18, IC107.18, IC108.18, IC109.18
unnamed: IC106.19, IC107.19, IC108.19, IC109.19
unnamed: IC106.20, IC107.20, IC108.20, IC109.20
unnamed: IC106.21, IC107.21, IC108.21, IC109.21
unnamed: IC106.22, IC107.22, IC108.22, IC109.22
unnamed: IC106.23, IC107.23, IC108.23, IC109.23
unnamed: IC106.24, IC107.24, IC108.24, IC109.24
unnamed: IC110.1, IC111.1, IC112.1, IC113.1
unnamed: IC110.2, IC111.2, IC112.2, IC113.2
unnamed: IC110.3, IC111.3, IC112.3, IC113.3
unnamed: IC110.4, IC111.4, IC112.4, IC113.4
unnamed: IC110.5, IC111.5, IC112.5, IC113.5
unnamed: IC110.6, IC111.6, IC112.6, IC113.6
unnamed: IC110.7, IC111.7, IC112.7, IC113.7
unnamed: IC110.8, IC111.8, IC112.8, IC113.8
unnamed: IC110.9, IC111.9, IC112.9, IC113.9
unnamed: IC110.10, IC111.10, IC112.10, IC113.10
unnamed: IC110.11, IC111.11, IC112.11, IC113.11
unnamed: IC110.12, IC111.12, IC112.12, IC113.12
unnamed: IC110.13, IC111.13, IC112.13, IC113.13
unnamed: IC110.14, IC111.14, IC112.14, IC113.14
unnamed: IC110.15, IC111.15, IC112.15, IC113.15
unnamed: IC110.16, IC111.16, IC112.16, IC113.16
unnamed: IC110.17, IC111.17, IC112.17, IC113.17
unnamed: IC110.18, IC111.18, IC112.18, IC113.18
unnamed: IC110.19, IC111.19, IC112.19, IC113.19
unnamed: IC110.20, IC111.20, IC112.20, IC113.20
unnamed: IC110.21, IC111.21, IC112.21, IC113.21
unnamed: IC110.22, IC111.22, IC112.22, IC113.22
unnamed: IC110.23, IC111.23, IC112.23, IC113.23
unnamed: IC110.24, IC111.24, IC112.24, IC113.24
unnamed: IC114.1, IC115.1, IC116.1, IC117.1
unnamed: IC114.2, IC115.2, IC116.2, IC117.2
unnamed: IC114.3, IC115.3, IC116.3, IC117.3
unnamed: IC114.4, IC115.4, IC116.4, IC117.4
unnamed: IC114.5, IC115.5, IC116.5, IC117.5
unnamed: IC114.6, IC115.6, IC116.6, IC117.6
unnamed: IC114.7, IC115.7, IC116.7, IC117.7
unnamed: IC114.8, IC115.8, IC116.8, IC117.8
unnamed: IC114.9, IC115.9, IC116.9, IC117.9
unnamed: IC114.10, IC115.10, IC116.10, IC117.10
unnamed: IC114.11, IC115.11, IC116.11, IC117.11
unnamed: IC114.12, IC115.12, IC116.12, IC117.12
unnamed: IC114.13, IC115.13, IC116.13, IC117.13
unnamed: IC114.14, IC115.14, IC116.14, IC117.14
unnamed: IC114.15, IC115.15, IC116.15, IC117.15
unnamed: IC114.16, IC115.16, IC116.16, IC117.16
unnamed: IC114.17, IC115.17, IC116.17, IC117.17
unnamed: IC114.18, IC115.18, IC116.18, IC117.18
unnamed: IC114.19, IC115.19, IC116.19, IC117.19
unnamed: IC114.20, IC115.20, IC116.20, IC117.20
unnamed: IC114.21, IC115.21, IC116.21, IC117.21
unnamed: IC114.22, IC115.22, IC116.22, IC117.22
unnamed: IC114.23, IC115.23, IC116.23, IC117.23
unnamed: IC114.24, IC115.24, IC116.24, IC117.24
unnamed: IC118.1, IC119.1, IC120.1, IC121.1
unnamed: IC118.2, IC119.2, IC120.2, IC121.2
unnamed: IC118.3, IC119.3, IC120.3, IC121.3
unnamed: IC118.4, IC119.4, IC120.4, IC121.4
unnamed: IC118.5, IC119.5, IC120.5, IC121.5
unnamed: IC118.6, IC119.6, IC120.6, IC121.6
unnamed: IC118.7, IC119.7, IC120.7, IC121.7
unnamed: IC118.8, IC119.8, IC120.8, IC121.8
unnamed: IC118.9, IC119.9, IC120.9, IC121.9
unnamed: IC118.10, IC119.10, IC120.10, IC121.10
unnamed: IC118.11, IC119.11, IC120.11, IC121.11
unnamed: IC118.12, IC119.12, IC120.12, IC121.12
unnamed: IC118.13, IC119.13, IC120.13, IC121.13
unnamed: IC118.14, IC119.14, IC120.14, IC121.14
unnamed: IC118.15, IC119.15, IC120.15, IC121.15
unnamed: IC118.16, IC119.16, IC120.16, IC121.16
unnamed: IC118.17, IC119.17, IC120.17, IC121.17
unnamed: IC118.18, IC119.18, IC120.18, IC121.18
unnamed: IC118.19, IC119.19, IC120.19, IC121.19
unnamed: IC118.20, IC119.20, IC120.20, IC121.20
unnamed: IC118.21, IC119.21, IC120.21, IC121.21
unnamed: IC118.22, IC119.22, IC120.22, IC121.22
unnamed: IC118.23, IC119.23, IC120.23, IC121.23
unnamed: IC118.24, IC119.24, IC120.24, IC121.24
unnamed: IC122.1, IC123.1, IC124.1, IC125.1
unnamed: IC122.2, IC123.2, IC124.2, IC125.2
unnamed: IC122.3, IC123.3, IC124.3, IC125.3
unnamed: IC122.4, IC123.4, IC124.4, IC125.4
unnamed: IC122.5, IC123.5, IC124.5, IC125.5
unnamed: IC122.6, IC123.6, IC124.6, IC125.6
unnamed: IC122.7, IC123.7, IC124.7, IC125.7
unnamed: IC122.8, IC123.8, IC124.8, IC125.8
unnamed: IC122.9, IC123.9, IC124.9, IC125.9
unnamed: IC122.10, IC123.10, IC124.10, IC125.10
unnamed: IC122.11, IC123.11, IC124.11, IC125.11
unnamed: IC122.12, IC123.12, IC124.12, IC125.12
unnamed: IC122.13, IC123.13, IC124.13, IC125.13
unnamed: IC122.14, IC123.14, IC124.14, IC125.14
unnamed: IC122.15, IC123.15, IC124.15, IC125.15
unnamed: IC122.16, IC123.16, IC124.16, IC125.16
unnamed: IC122.17, IC123.17, IC124.17, IC125.17
unnamed: IC122.18, IC123.18, IC124.18, IC125.18
unnamed: IC122.19, IC123.19, IC124.19, IC125.19
unnamed: IC122.20, IC123.20, IC124.20, IC125.20
unnamed: IC122.21, IC123.21, IC124.21, IC125.21
unnamed: IC122.22, IC123.22, IC124.22, IC125.22
unnamed: IC122.23, IC123.23, IC124.23, IC125.23
unnamed: IC122.24, IC123.24, IC124.24, IC125.24
unnamed: IC126.1, IC127.1, IC128.1, IC129.1
unnamed: IC126.2, IC127.2, IC128.2, IC129.2
unnamed: IC126.3, IC127.3, IC128.3, IC129.3
unnamed: IC126.4, IC127.4, IC128.4, IC129.4
unnamed: IC126.5, IC127.5, IC128.5, IC129.5
unnamed: IC126.6, IC127.6, IC128.6, IC129.6
unnamed: IC126.7, IC127.7, IC128.7, IC129.7
unnamed: IC126.8, IC127.8, IC128.8, IC129.8
unnamed: IC126.9, IC127.9, IC128.9, IC129.9
unnamed: IC126.10, IC127.10, IC128.10, IC129.10
unnamed: IC126.11, IC127.11, IC128.11, IC129.11
unnamed: IC126.12, IC127.12, IC128.12, IC129.12
unnamed: IC126.13, IC127.13, IC128.13, IC129.13
unnamed: IC126.14, IC127.14, IC128.14, IC129.14
unnamed: IC126.15, IC127.15, IC128.15, IC129.15
unnamed: IC126.16, IC127.16, IC128.16, IC129.16
unnamed: IC126.17, IC127.17, IC128.17, IC129.17
unnamed: IC126.18, IC127.18, IC128.18, IC129.18
unnamed: IC126.19, IC127.19, IC128.19, IC129.19
unnamed: IC126.20, IC127.20, IC128.20, IC129.20
unnamed: IC126.21, IC127.21, IC128.21, IC129.21
unnamed: IC126.22, IC127.22, IC128.22, IC129.22
unnamed: IC126.23, IC127.23, IC128.23, IC129.23
unnamed: IC126.24, IC127.24, IC128.24, IC129.24
unnamed: IC130.1, IC131.1, IC132.1, IC133.1
unnamed: IC130.2, IC131.2, IC132.2, IC133.2
unnamed: IC130.3, IC131.3, IC132.3, IC133.3
unnamed: IC130.4, IC131.4, IC132.4, IC133.4
unnamed: IC130.5, IC131.5, IC132.5, IC133.5
unnamed: IC130.6, IC131.6, IC132.6, IC133.6
unnamed: IC130.7, IC131.7, IC132.7, IC133.7
unnamed: IC130.8, IC131.8, IC132.8, IC133.8
unnamed: IC130.9, IC131.9, IC132.9, IC133.9
unnamed: IC130.10, IC131.10, IC132.10, IC133.10
unnamed: IC130.11, IC131.11, IC132.11, IC133.11
unnamed: IC130.12, IC131.12, IC132.12, IC133.12
unnamed: IC130.13, IC131.13, IC132.13, IC133.13
unnamed: IC130.14, IC131.14, IC132.14, IC133.14
unnamed: IC130.15, IC131.15, IC132.15, IC133.15
unnamed: IC130.16, IC131.16, IC132.16, IC133.16
unnamed: IC130.17, IC131.17, IC132.17, IC133.17
unnamed: IC130.18, IC131.18, IC132.18, IC133.18
unnamed: IC130.19, IC131.19, IC132.19, IC133.19
unnamed: IC130.20, IC131.20, IC132.20, IC133.20
unnamed: IC130.21, IC131.21, IC132.21, IC133.21
unnamed: IC130.22, IC131.22, IC132.22, IC133.22
unnamed: IC130.23, IC131.23, IC132.23, IC133.23
unnamed: IC130.24, IC131.24, IC132.24, IC133.24
unnamed: IC134.1, IC135.1, IC136.1, IC137.1
unnamed: IC134.2, IC135.2, IC136.2, IC137.2
unnamed: IC134.3, IC135.3, IC136.3, IC137.3
unnamed: IC134.4, IC135.4, IC136.4, IC137.4
unnamed: IC134.5, IC135.5, IC136.5, IC137.5
unnamed: IC134.6, IC135.6, IC136.6, IC137.6
unnamed: IC134.7, IC135.7, IC136.7, IC137.7
unnamed: IC134.8, IC135.8, IC136.8, IC137.8
unnamed: IC134.9, IC135.9, IC136.9, IC137.9
unnamed: IC134.10, IC135.10, IC136.10, IC137.10
unnamed: IC134.11, IC135.11, IC136.11, IC137.11
unnamed: IC134.12, IC135.12, IC136.12, IC137.12
unnamed: IC134.13, IC135.13, IC136.13, IC137.13
unnamed: IC134.14, IC135.14, IC136.14, IC137.14
unnamed: IC134.15, IC135.15, IC136.15, IC137.15
unnamed: IC134.16, IC135.16, IC136.16, IC137.16
unnamed: IC134.17, IC135.17, IC136.17, IC137.17
unnamed: IC134.18, IC135.18, IC136.18, IC137.18
unnamed: IC134.19, IC135.19, IC136.19, IC137.19
unnamed: IC134.20, IC135.20, IC136.20, IC137.20
unnamed: IC134.21, IC135.21, IC136.21, IC137.21
unnamed: IC134.22, IC135.22, IC136.22, IC137.22
unnamed: IC134.23, IC135.23, IC136.23, IC137.23
unnamed: IC134.24, IC135.24, IC136.24, IC137.24
unnamed: IC138.1, IC139.1, IC140.1, IC141.1
unnamed: IC138.2, IC139.2, IC140.2, IC141.2
unnamed: IC138.3, IC139.3, IC140.3, IC141.3
unnamed: IC138.4, IC139.4, IC140.4, IC141.4
unnamed: IC138.5, IC139.5, IC140.5, IC141.5
unnamed: IC138.6, IC139.6, IC140.6, IC141.6
unnamed: IC138.7, IC139.7, IC140.7, IC141.7
unnamed: IC138.8, IC139.8, IC140.8, IC141.8
unnamed: IC138.9, IC139.9, IC140.9, IC141.9
unnamed: IC138.10, IC139.10, IC140.10, IC141.10
unnamed: IC138.11, IC139.11, IC140.11, IC141.11
unnamed: IC138.12, IC139.12, IC140.12, IC141.12
unnamed: IC138.13, IC139.13, IC140.13, IC141.13
unnamed: IC138.14, IC139.14, IC140.14, IC141.14
unnamed: IC138.15, IC139.15, IC140.15, IC141.15
unnamed: IC138.16, IC139.16, IC140.16, IC141.16
unnamed: IC138.17, IC139.17, IC140.17, IC141.17
unnamed: IC138.18, IC139.18, IC140.18, IC141.18
unnamed: IC138.19, IC139.19, IC140.19, IC141.19
unnamed: IC138.20, IC139.20, IC140.20, IC141.20
unnamed: IC138.21, IC139.21, IC140.21, IC141.21
unnamed: IC138.22, IC139.22, IC140.22, IC141.22
unnamed: IC138.23, IC139.23, IC140.23, IC141.23
unnamed: IC138.24, IC139.24, IC140.24, IC141.24
unnamed: IC142.1, IC143.1, IC144.1, IC145.1
unnamed: IC142.2, IC143.2, IC144.2, IC145.2
unnamed: IC142.3, IC143.3, IC144.3, IC145.3
unnamed: IC142.4, IC143.4, IC144.4, IC145.4
unnamed: IC142.5, IC143.5, IC144.5, IC145.5
unnamed: IC142.6, IC143.6, IC144.6, IC145.6
unnamed: IC142.7, IC143.7, IC144.7, IC145.7
unnamed: IC142.8, IC143.8, IC144.8, IC145.8
unnamed: IC142.9, IC143.9, IC144.9, IC145.9
unnamed: IC142.10, IC143.10, IC144.10, IC145.10
unnamed: IC142.11, IC143.11, IC144.11, IC145.11
unnamed: IC142.12, IC143.12, IC144.12, IC145.12
unnamed: IC142.13, IC143.13, IC144.13, IC145.13
unnamed: IC142.14, IC143.14, IC144.14, IC145.14
unnamed: IC142.15, IC143.15, IC144.15, IC145.15
unnamed: IC142.16, IC143.16, IC144.16, IC145.16
unnamed: IC142.17, IC143.17, IC144.17, IC145.17
unnamed: IC142.18, IC143.18, IC144.18, IC145.18
unnamed: IC142.19, IC143.19, IC144.19, IC145.19
unnamed: IC142.20, IC143.20, IC144.20, IC145.20
unnamed: IC142.21, IC143.21, IC144.21, IC145.21
unnamed: IC142.22, IC143.22, IC144.22, IC145.22
unnamed: IC142.23, IC143.23, IC144.23, IC145.23
unnamed: IC142.24, IC143.24, IC144.24, IC145.24
unnamed: IC146.1, IC147.1, IC148.1, IC149.1
unnamed: IC146.2, IC147.2, IC148.2, IC149.2
unnamed: IC146.3, IC147.3, IC148.3, IC149.3
unnamed: IC146.4, IC147.4, IC148.4, IC149.4
unnamed: IC146.5, IC147.5, IC148.5, IC149.5
unnamed: IC146.6, IC147.6, IC148.6, IC149.6
unnamed: IC146.7, IC147.7, IC148.7, IC149.7
unnamed: IC146.8, IC147.8, IC148.8, IC149.8
unnamed: IC146.9, IC147.9, IC148.9, IC149.9
unnamed: IC146.10, IC147.10, IC148.10, IC149.10
unnamed: IC146.11, IC147.11, IC148.11, IC149.11
unnamed: IC146.12, IC147.12, IC148.12, IC149.12
unnamed: IC146.13, IC147.13, IC148.13, IC149.13
unnamed: IC146.14, IC147.14, IC148.14, IC149.14
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
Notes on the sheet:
General Prototyping Areas

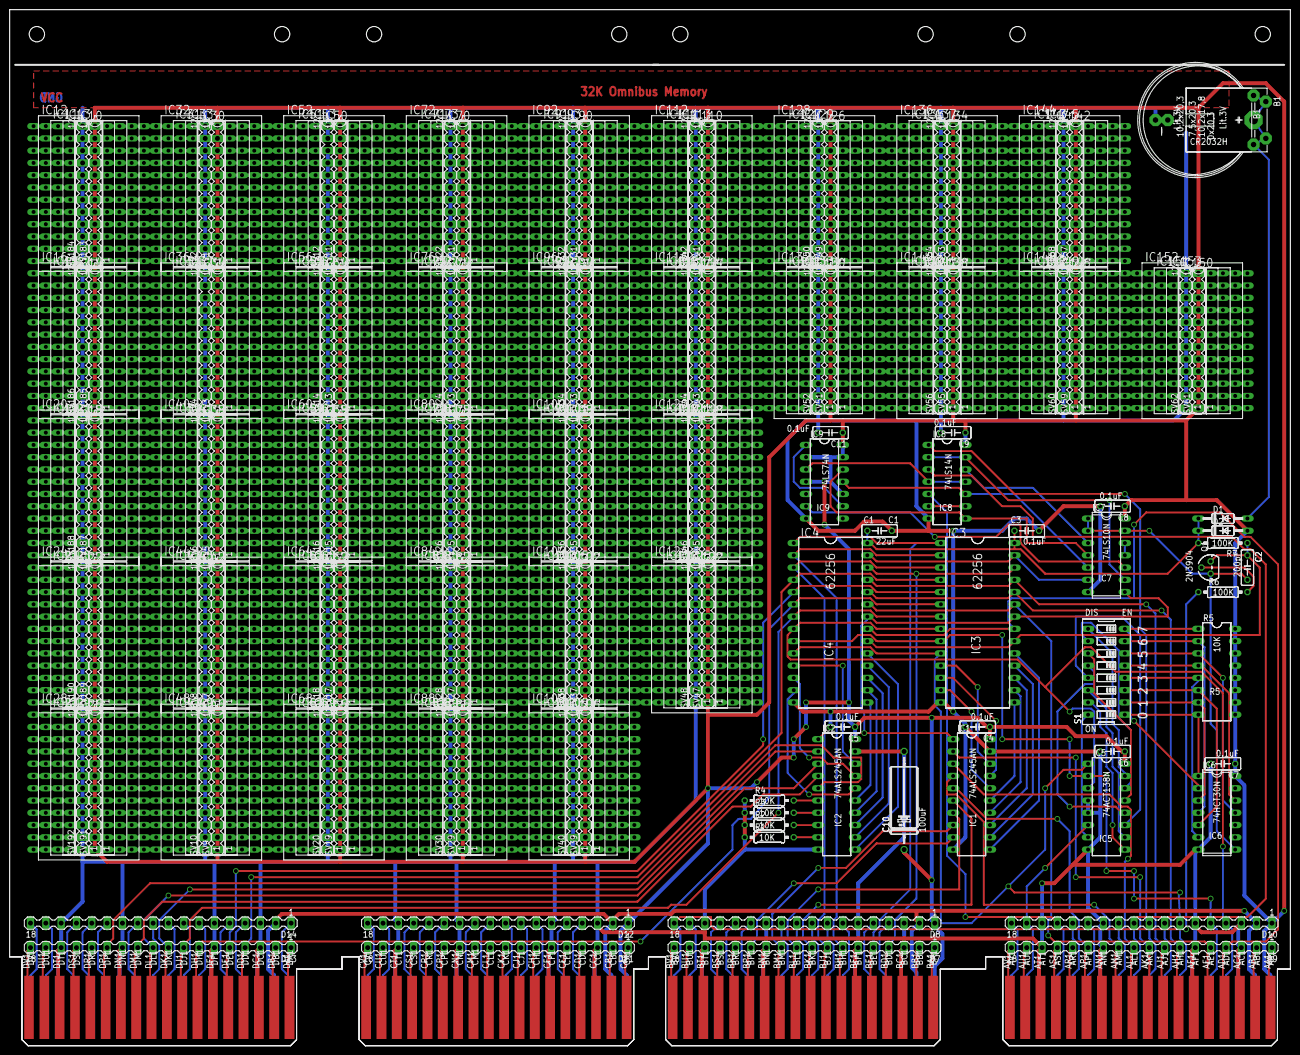
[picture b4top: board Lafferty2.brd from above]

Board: 2 copper layers, 265.3 x 214.6 mm, 258 parts (0 on the bottom side), 1024 nets.
